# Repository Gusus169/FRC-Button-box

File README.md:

# FRC Button box
Reliability is critical in FIRST Robotics Competition (FRC), especially during matches where a single equipment failure can affect an entire game. One component that many teams depend on is a button box, which provides drivers with quick access to robot functions that would otherwise be difficult to control through a standard controller alone. Rather than relying on a commercially available solution, I decided to design a custom button box PCB tailored to my team's needs.

The goal of this project was to create a professional, competition-ready button box featuring plug-in terminals, an OLED display for testing and diagnostics, an indicator LED, and a large logo of my FRC Team 5402, Wreckless Robotics, integrated directly into the PCB design. Throughout the project, I researched existing button boxes used by other FRC teams, selected components through DigiKey, designed the schematic in KiCad, created the PCB layout, and prepared the board for manufacturing. Along the way, I learned more about PCB design, component libraries, footprint management, routing techniques, and design-for-manufacturing considerations.

This repository documents the complete development process, including planning, schematic design, PCB layout, manufacturing files, and project documentation. The finished design will be used to support driver practice and competition preparation for Team 5402 while providing a reliable and maintainable control interface for future seasons.

# 3D View of Final PCB Design-

Front-

Back-

# Key Features 
-Large Team Logo (very important)
-Flexibility – features 30 independent ports where buttons can be plugged in; no fixed sequence required, just plug-and-play

-Buttons can be swapped or replaced within a minute
  
-Uses a Raspberry Pi Pico (RP2040), allowing buttons to be programmed as needed for different FRC sessions

-Supports advanced logic such as button pairing and conditional inputs

-Designed for reliability – minimal excess components, reducing potential points of failure

-Includes an indicator LED for button box status

-Features a 0.91" OLED display for individual button testing and diagnostics

-Includes mounting holes to securely fasten the PCB in an enclosure or driver station setup

# Schematic & PCB DESIGN 

Schematic- 

PCB Front-

PCB Back-

# BOM

| Qty | Component                | Value / Part Number        |
| --- | ------------------------ | -------------------------- |
| 1   | OLED Display             | SSD1306 0.91" 128×32       |
| 1   | LED                      | 3mm LED                    |
| 30  | Diode                    | 1N4148W                    |
| 6   | Terminal Block Connector | Phoenix 1792944            |
| 1   | Resistor                 | 330 Ω                      |
| 1   | Microcontroller          | Raspberry Pi Pico (RP2040) |

# License

MIT

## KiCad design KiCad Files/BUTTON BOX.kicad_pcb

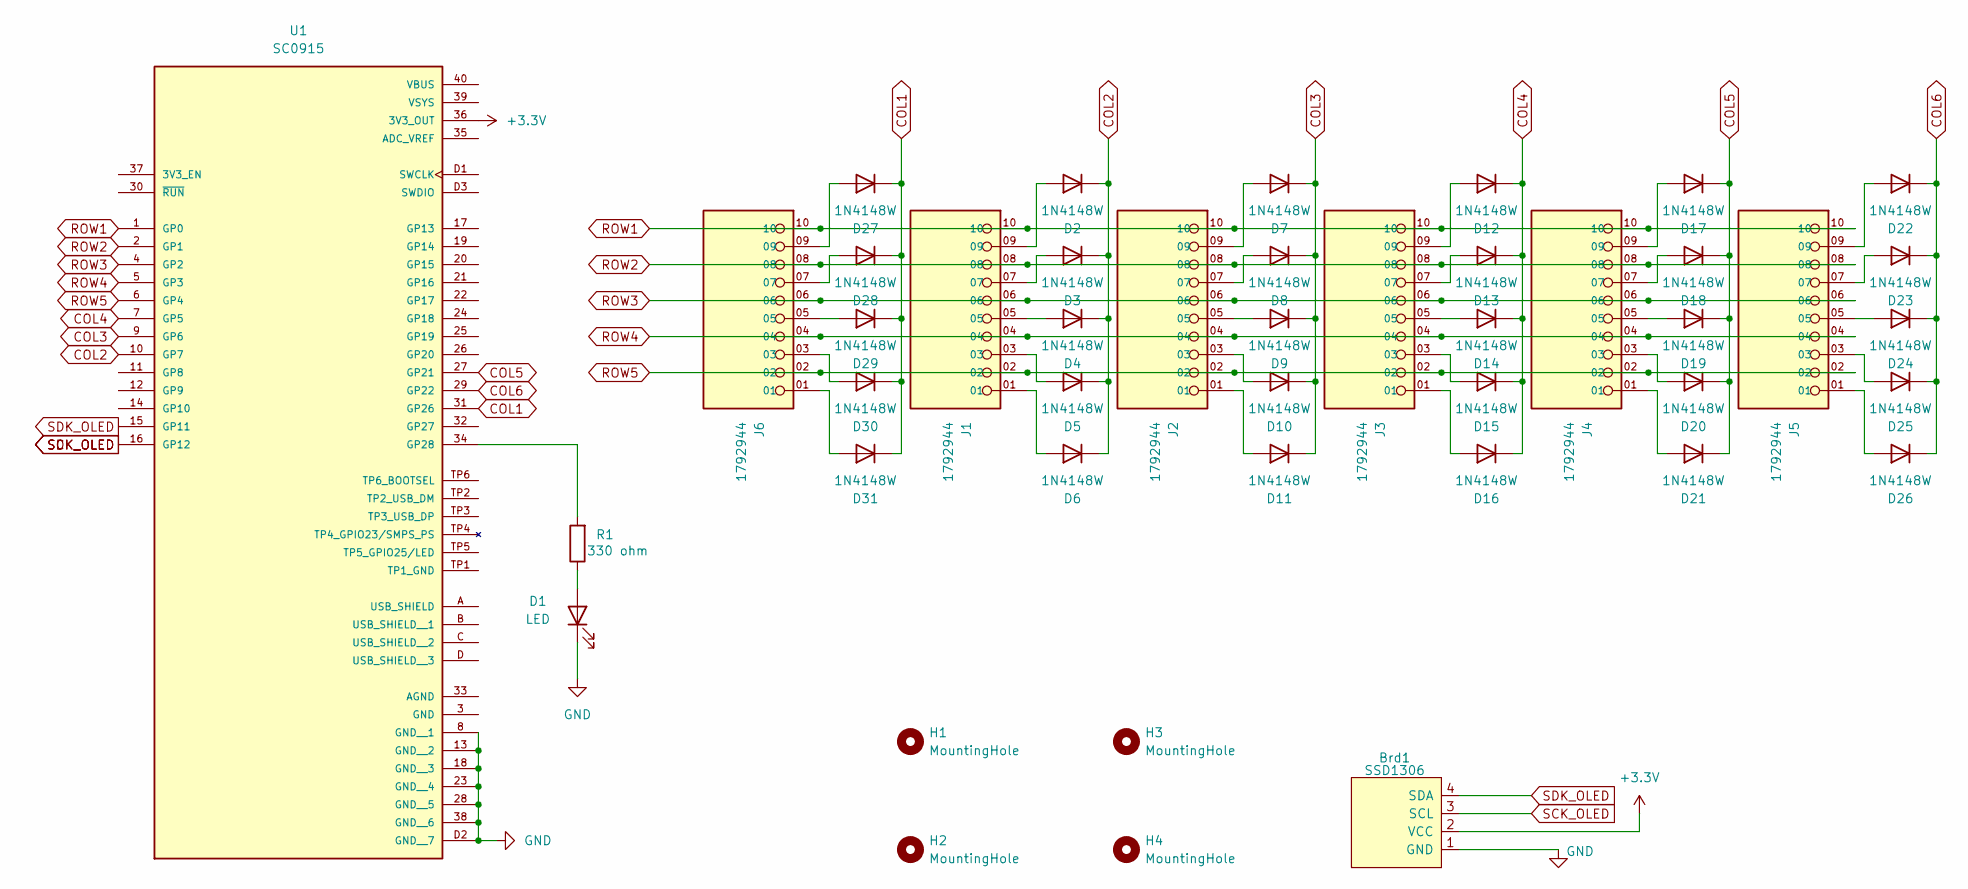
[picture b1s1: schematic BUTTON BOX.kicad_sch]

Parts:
Brd1: SSD1306; SSD1306-0.91-OLED-4pin-128x32
D1: LED; LED_D3.0mm
D2, D3, D4, D5, D6, D7, D8, D9, D10, D11, D12, D13, D14, D15, D16, D17, D18, D19, D20, D21, D22, D23, D24, D25, D26, D27, D28, D29, D30, D31: 1N4148W; D_SOD-123
H1, H2, H3, H4: MountingHole; MountingHole_3.2mm_M3
J1, J2, J3, J4, J5, J6: 1792944; PHOENIX_1792944; PARTREV 12.08.2015
R1: 330 ohm; R_0805_2012Metric_Pad1.20x1.40mm_HandSolder
U1: SC0915; RaspberryPi_Pico_Common_Unspecified; PARTREV 1.9

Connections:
+3.3V: Brd1.2 (VCC), U1.36 (3V3_OUT)
COL1: D27.1 (K), D28.1 (K), D29.1 (K), D30.1 (K), D31.1 (K), U1.31 (GP26)
COL2: D2.1 (K), D3.1 (K), D4.1 (K), D5.1 (K), D6.1 (K), U1.10 (GP7)
COL3: D7.1 (K), D8.1 (K), D9.1 (K), D10.1 (K), D11.1 (K), U1.9 (GP6)
COL4: D12.1 (K), D13.1 (K), D14.1 (K), D15.1 (K), D16.1 (K), U1.7 (GP5)
COL5: D17.1 (K), D18.1 (K), D19.1 (K), D20.1 (K), D21.1 (K), U1.27 (GP21)
COL6: D22.1 (K), D23.1 (K), D24.1 (K), D25.1 (K), D26.1 (K), U1.29 (GP22)
GND: Brd1.1 (GND), D1.1 (K), U1.8 (GND__1), U1.13 (GND__2), U1.18 (GND__3), U1.23 (GND__4), U1.28 (GND__5), U1.38 (GND__6), U1.D2 (GND__7)
unnamed: D1.2 (A), R1.1
unnamed: D2.2 (A), J1.09
unnamed: D3.2 (A), J1.07
unnamed: D4.2 (A), J1.05
unnamed: D5.2 (A), J1.03
unnamed: D6.2 (A), J1.01
unnamed: D7.2 (A), J2.09
unnamed: D8.2 (A), J2.07
unnamed: D9.2 (A), J2.05
unnamed: D10.2 (A), J2.03
unnamed: D11.2 (A), J2.01
unnamed: D12.2 (A), J3.09
unnamed: D13.2 (A), J3.07
unnamed: D14.2 (A), J3.05
unnamed: D15.2 (A), J3.03
unnamed: D16.2 (A), J3.01
unnamed: D17.2 (A), J4.09
unnamed: D18.2 (A), J4.07
unnamed: D19.2 (A), J4.05
unnamed: D20.2 (A), J4.03
unnamed: D21.2 (A), J4.01
unnamed: D22.2 (A), J5.09
unnamed: D23.2 (A), J5.07
unnamed: D24.2 (A), J5.05
unnamed: D25.2 (A), J5.03
unnamed: D26.2 (A), J5.01
unnamed: D27.2 (A), J6.09
unnamed: D28.2 (A), J6.07
unnamed: D29.2 (A), J6.05
unnamed: D30.2 (A), J6.03
unnamed: D31.2 (A), J6.01
unnamed: R1.2, U1.34 (GP28)
ROW1: J1.10, J2.10, J3.10, J4.10, J5.10, J6.10, U1.1 (GP0)
ROW2: J1.08, J2.08, J3.08, J4.08, J5.08, J6.08, U1.2 (GP1)
ROW3: J1.06, J2.06, J3.06, J4.06, J5.06, J6.06, U1.4 (GP2)
ROW4: J1.04, J2.04, J3.04, J4.04, J5.04, J6.04, U1.5 (GP3)
ROW5: J1.02, J2.02, J3.02, J4.02, J5.02, J6.02, U1.6 (GP4)

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
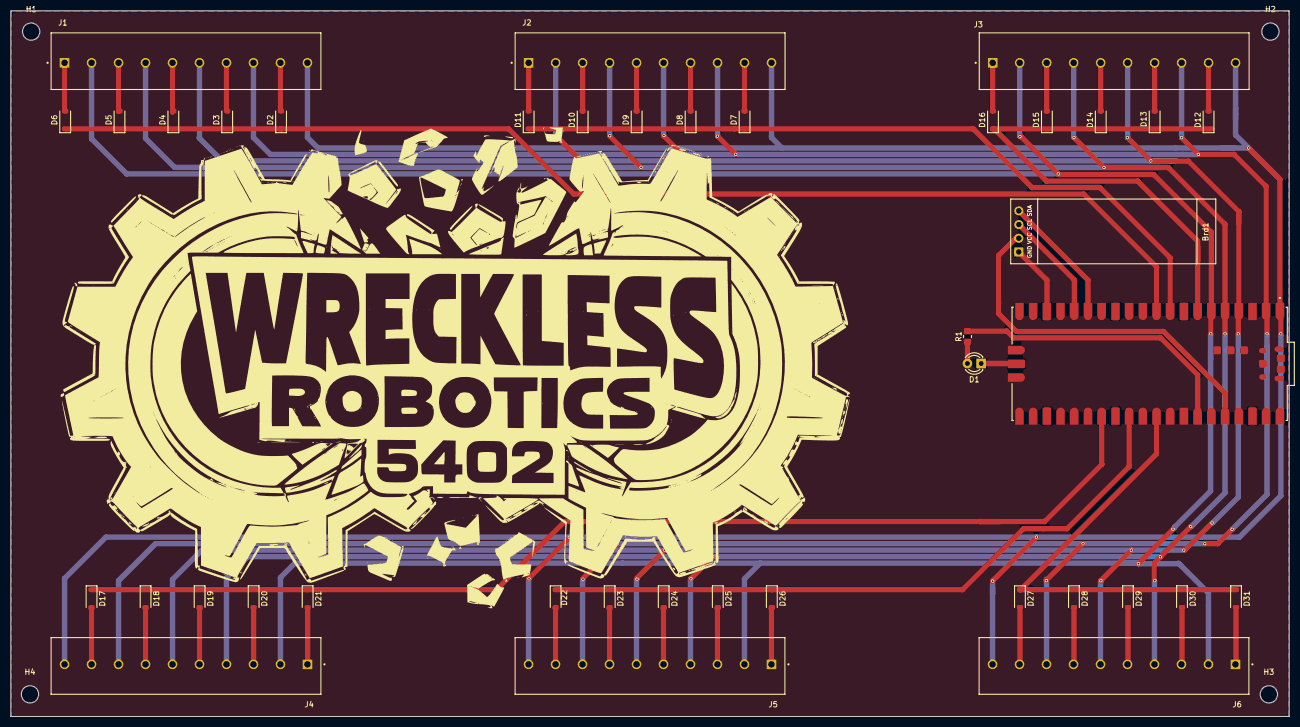
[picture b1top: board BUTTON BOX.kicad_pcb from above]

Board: 2 copper layers, 236.8 x 130.7 mm, 44 parts (0 on the bottom side), 47 nets.

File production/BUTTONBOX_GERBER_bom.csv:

Designator,Footprint,Quantity,Value,LCSC Part #
BRD1,SSD1306-0.91-OLED-4pin-128x32,1,SSD1306,
D1,LED_D3.0mm,1,LED,
"D10, D11, D12, D13, D14, D15, D16, D17, D18, D19, D2, D20, D21, D22, D23, D24, D25, D26, D27, D28, D29, D3, D30, D31, D4, D5, D6, D7, D8, D9",D_SOD-123,30,1N4148W,
"J1, J2, J3, J4, J5, J6",PHOENIX_1792944,6,1792944,
R1,0805,1,330 ohm,
U1,pi pico,1,SC0915,

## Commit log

2026-06-07 All the KiCad Files
2026-06-07 README
    Updated project description and key features for the FRC Button Box.
2026-06-07 Firmware for the device
2026-06-12 Manufacturing ready files!
2026-06-23 UN-ZIPPED Files
2026-06-23 Remove zip file
